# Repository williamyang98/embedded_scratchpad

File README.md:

## Embedded Scratchpad
Collection of random embedded projects

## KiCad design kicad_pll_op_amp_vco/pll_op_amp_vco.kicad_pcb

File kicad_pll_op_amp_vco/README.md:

# Introduction
Type 1 Phased Locked Loop (PLL) that synchronises to an external clock signal by divisions of 2^N for N >= 0
- 74HC4040 counter to create clock feedback signals at ```f_out = f_in/2^N```
- 74HC86 XOR to create crude digital phase detector that creates an error signal between the phase of the input and output signals
- LM358 to create variable frequency triangular wave
- LM2901 comparator to turn the triangular wave into a square signal

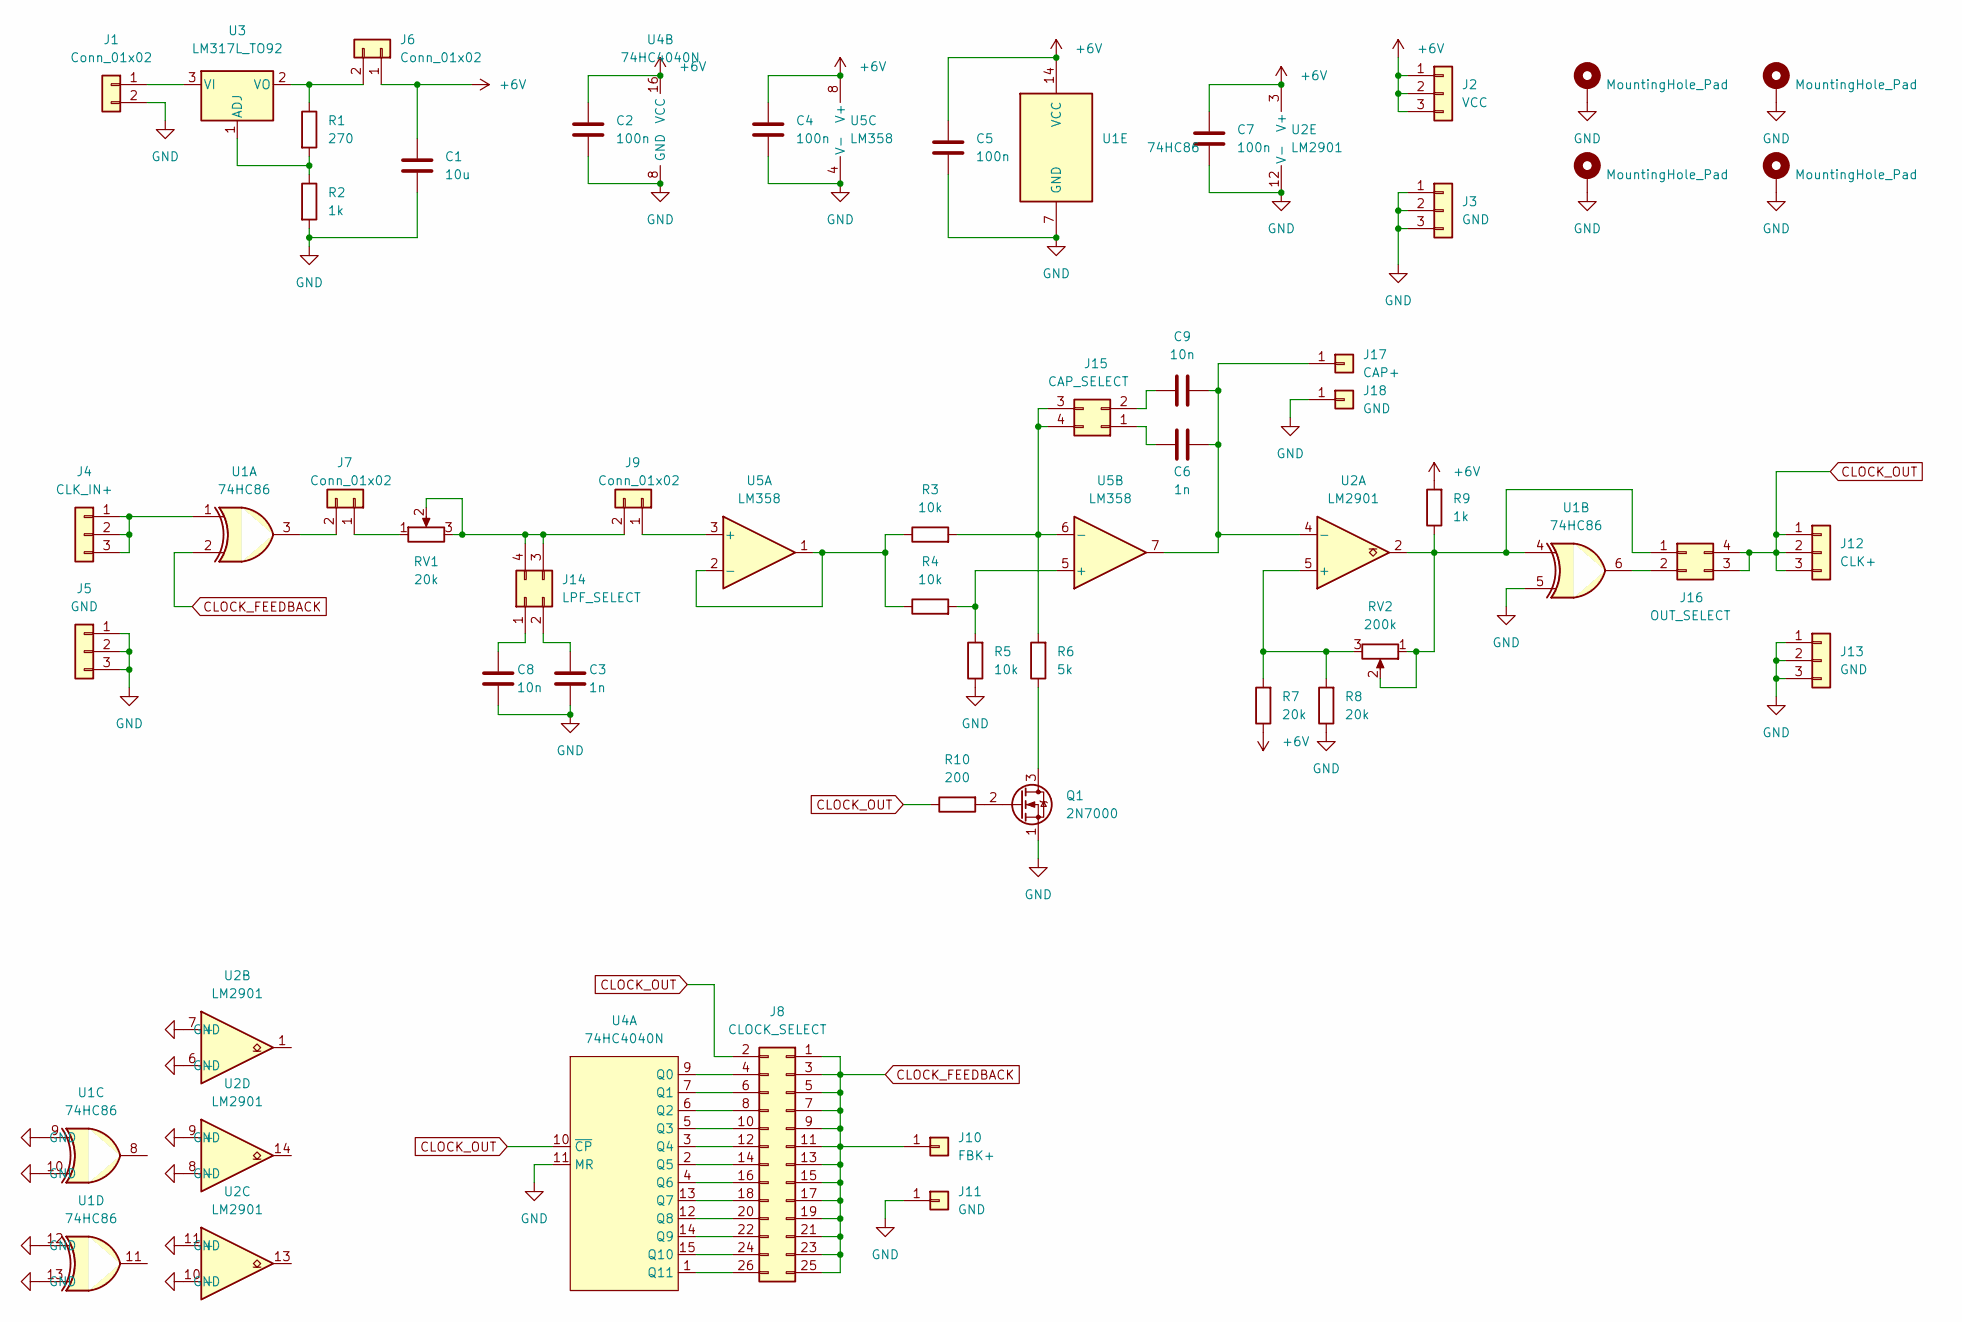
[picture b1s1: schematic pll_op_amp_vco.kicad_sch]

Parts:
C1: 10u; CP_Radial_D4.0mm_P2.00mm
C2, C4, C5, C7: 100n; C_Disc_D5.0mm_W2.5mm_P5.00mm
C3, C6: 1n; C_Disc_D5.0mm_W2.5mm_P5.00mm
C8, C9: 10n; C_Disc_D5.0mm_W2.5mm_P5.00mm
H1, H2, H3, H4: MountingHole_Pad; MountingHole_2.5mm_Pad_Via
J1: Conn_01x02; JST_EH_B2B-EH-A_1x02_P2.50mm_Vertical
J2: VCC; PinHeader_1x03_P2.54mm_Vertical
J3, J5, J13: GND; PinHeader_1x03_P2.54mm_Vertical
J4: CLK_IN+; PinHeader_1x03_P2.54mm_Vertical
J6, J7, J9: Conn_01x02; PinHeader_1x02_P2.54mm_Vertical
J8: CLOCK_SELECT; PinHeader_2x13_P2.54mm_Vertical
J10: FBK+; PinHeader_1x01_P2.54mm_Vertical
J11, J18: GND; PinHeader_1x01_P2.54mm_Vertical
J12: CLK+; PinHeader_1x03_P2.54mm_Vertical
J14: LPF_SELECT; PinHeader_2x02_P2.54mm_Vertical
J15: CAP_SELECT; PinHeader_2x02_P2.54mm_Vertical
J16: OUT_SELECT; PinHeader_2x02_P2.54mm_Vertical
J17: CAP+; PinHeader_1x01_P2.54mm_Vertical
Q1: 2N7000; TO-92_Inline
R1: 270; R_Axial_DIN0207_L6.3mm_D2.5mm_P7.62mm_Horizontal
R2, R9: 1k; R_Axial_DIN0207_L6.3mm_D2.5mm_P7.62mm_Horizontal
R3, R4, R5: 10k; R_Axial_DIN0207_L6.3mm_D2.5mm_P7.62mm_Horizontal
R6: 5k; R_Axial_DIN0207_L6.3mm_D2.5mm_P7.62mm_Horizontal
R7, R8: 20k; R_Axial_DIN0207_L6.3mm_D2.5mm_P7.62mm_Horizontal
R10: 200; R_Axial_DIN0207_L6.3mm_D2.5mm_P7.62mm_Horizontal
RV1: 20k; Potentiometer_ACP_CA9-H5_Horizontal
RV2: 200k; Potentiometer_ACP_CA9-H5_Horizontal
U1: 74HC86; DIP-14_W7.62mm_Socket_LongPads
U2: LM2901; DIP-14_W7.62mm_Socket_LongPads
U3: LM317L_TO92; TO-92_Inline
U4: 74HC4040N; DIP-16_W7.62mm_Socket_LongPads
U5: LM358; DIP-8_W7.62mm_Socket_LongPads

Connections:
+6V: C1.1, C2.2, C4.2, C5.2, C7.2, J2.1, J2.2, J2.3, J6.1, R7.1, R9.2, U1.14 (VCC), U2.3 (V+), U4.16 (VCC), U5.8 (V+)
CLOCK_FEEDBACK: J8.1, J8.3, J8.5, J8.7, J8.9, J8.11, J8.13, J8.15, J8.17, J8.19, J8.21, J8.23, J8.25, J10.1, U1.2
CLOCK_OUT: J8.2, J12.1, J12.2, J12.3, J16.3, J16.4, R10.1, U4.10 (~CP)
GND: C1.2, C2.1, C3.1, C4.1, C5.1, C7.1, C8.1, H1.1, H2.1, H3.1, H4.1, J1.2, J3.1, J3.2, J3.3, J5.1, J5.2, J5.3, J11.1, J13.1, J13.2, J13.3, J18.1, Q1.1 (S), R2.2, R5.1, R8.1, U1.5, U1.7 (GND), U1.9, U1.10, U1.12, U1.13, U2.6 (-), U2.7 (+), U2.8 (-), U2.9 (+), U2.10 (-), U2.11 (+), U2.12 (V-), U4.8 (GND), U4.11 (MR), U5.4 (V-)
unnamed: C3.2, J14.2
unnamed: C6.1, J15.1
unnamed: C6.2, C9.2, J17.1, U2.4 (-), U5.7
unnamed: C8.2, J14.1
unnamed: C9.1, J15.2
unnamed: J1.1, U3.3 (VI)
unnamed: J4.1, J4.2, J4.3, U1.1
unnamed: J6.2, R1.1, U3.2 (VO)
unnamed: J7.1, RV1.1
unnamed: J7.2, U1.3
unnamed: J8.4, U4.9 (Q0)
unnamed: J8.6, U4.7 (Q1)
unnamed: J8.8, U4.6 (Q2)
unnamed: J8.10, U4.5 (Q3)
unnamed: J8.12, U4.3 (Q4)
unnamed: J8.14, U4.2 (Q5)
unnamed: J8.16, U4.4 (Q6)
unnamed: J8.18, U4.13 (Q7)
unnamed: J8.20, U4.12 (Q8)
unnamed: J8.22, U4.14 (Q9)
unnamed: J8.24, U4.15 (Q10)
unnamed: J8.26, U4.1 (Q11)
unnamed: J9.1, U5.3 (+)
unnamed: J9.2, J14.3, J14.4, RV1.2, RV1.3
unnamed: J15.3, J15.4, R3.2, R6.2, U5.6 (-)
unnamed: J16.1, R9.1, RV2.1, RV2.2, U1.4, U2.2
unnamed: J16.2, U1.6
unnamed: Q1.2 (G), R10.2
unnamed: Q1.3 (D), R6.1
unnamed: R1.2, R2.1, U3.1 (ADJ)
unnamed: R3.1, R4.1, U5.1, U5.2 (-)
unnamed: R4.2, R5.2, U5.5 (+)
unnamed: R7.2, R8.2, RV2.3, U2.5 (+)

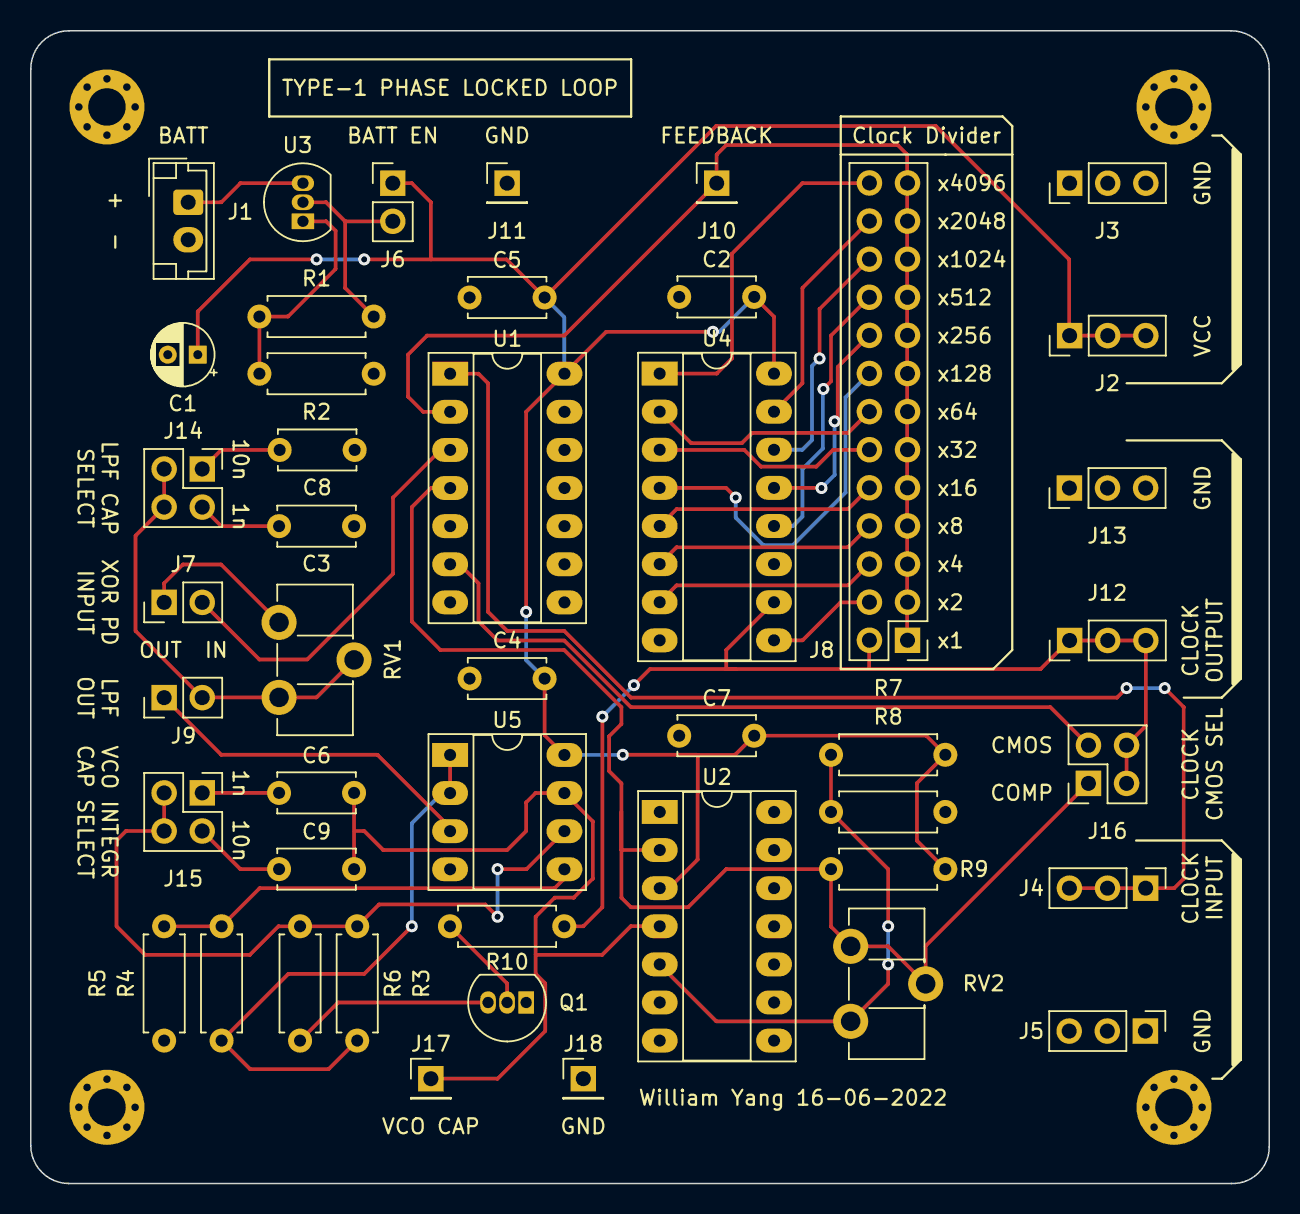
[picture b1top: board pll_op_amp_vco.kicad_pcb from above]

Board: 2 copper layers, 82.5 x 76.8 mm, 49 parts (0 on the bottom side), 37 nets.

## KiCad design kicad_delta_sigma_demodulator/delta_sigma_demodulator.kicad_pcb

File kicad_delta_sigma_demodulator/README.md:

# Introduction
Demodulates digital delta sigma serial signal into original analog signal using:
- LM319 comparators to clean up digital delta sigma 1bit signal
- LM324 op amps to create a multi-stage active low pass filter

It is the receiver board for the delta sigma modulator transmitter board in ```kicad_delta_sigma_modulator```.

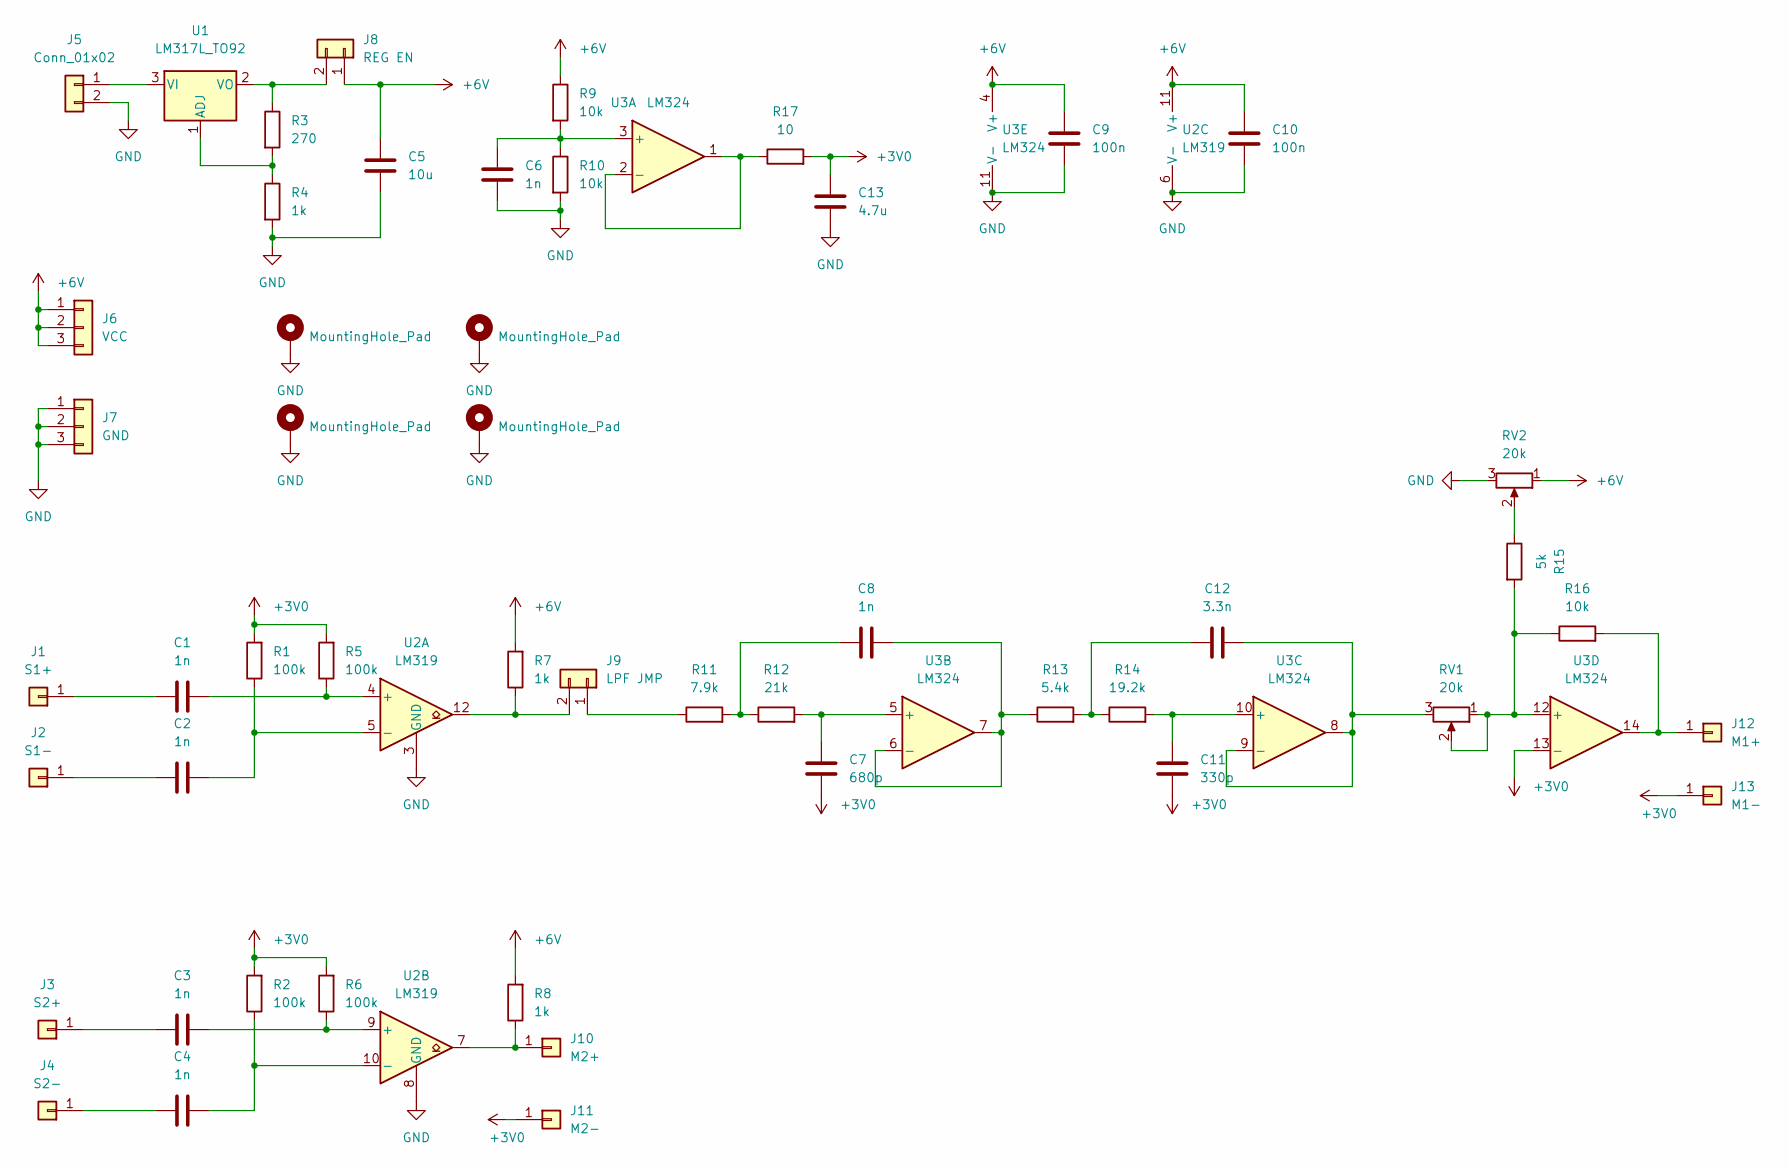
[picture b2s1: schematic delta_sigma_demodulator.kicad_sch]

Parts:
C1, C2, C3, C4, C6, C8: 1n; C_Disc_D5.0mm_W2.5mm_P5.00mm
C5: 10u; CP_Radial_D4.0mm_P2.00mm
C7: 680p; C_Disc_D5.0mm_W2.5mm_P5.00mm
C9, C10: 100n; C_Disc_D5.0mm_W2.5mm_P5.00mm
C11: 330p; C_Disc_D5.0mm_W2.5mm_P5.00mm
C12: 3.3n; C_Disc_D5.0mm_W2.5mm_P5.00mm
C13: 4.7u; CP_Radial_D4.0mm_P2.00mm
H1, H2, H3, H4: MountingHole_Pad; MountingHole_2.5mm_Pad_Via
J1: S1+; PinHeader_1x01_P2.54mm_Vertical
J2: S1-; PinHeader_1x01_P2.54mm_Vertical
J3: S2+; PinHeader_1x01_P2.54mm_Vertical
J4: S2-; PinHeader_1x01_P2.54mm_Vertical
J5: Conn_01x02; JST_EH_B2B-EH-A_1x02_P2.50mm_Vertical
J6: VCC; PinHeader_1x03_P2.54mm_Vertical
J7: GND; PinHeader_1x03_P2.54mm_Vertical
J8: REG EN; PinHeader_1x02_P2.54mm_Vertical
J9: LPF JMP; PinHeader_1x02_P2.54mm_Vertical
J10: M2+; PinHeader_1x01_P2.54mm_Vertical
J11: M2-; PinHeader_1x01_P2.54mm_Vertical
J12: M1+; PinHeader_1x01_P2.54mm_Vertical
J13: M1-; PinHeader_1x01_P2.54mm_Vertical
R1, R2, R5, R6: 100k; R_Axial_DIN0207_L6.3mm_D2.5mm_P7.62mm_Horizontal
R3: 270; R_Axial_DIN0207_L6.3mm_D2.5mm_P7.62mm_Horizontal
R4, R7, R8: 1k; R_Axial_DIN0207_L6.3mm_D2.5mm_P7.62mm_Horizontal
R9, R10, R16: 10k; R_Axial_DIN0207_L6.3mm_D2.5mm_P7.62mm_Horizontal
R11: 7.9k; R_Axial_DIN0207_L6.3mm_D2.5mm_P7.62mm_Horizontal
R12: 21k; R_Axial_DIN0207_L6.3mm_D2.5mm_P7.62mm_Horizontal
R13: 5.4k; R_Axial_DIN0207_L6.3mm_D2.5mm_P7.62mm_Horizontal
R14: 19.2k; R_Axial_DIN0207_L6.3mm_D2.5mm_P7.62mm_Horizontal
R15: 5k; R_Axial_DIN0207_L6.3mm_D2.5mm_P7.62mm_Horizontal
R17: 10; R_Axial_DIN0207_L6.3mm_D2.5mm_P7.62mm_Horizontal
RV1, RV2: 20k; Potentiometer_ACP_CA9-H5_Horizontal
U1: LM317L_TO92; TO-92_Inline
U2: LM319; DIP-14_W7.62mm_Socket_LongPads
U3: LM324; DIP-14_W7.62mm_Socket_LongPads

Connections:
+3V0: C7.2, C11.2, C13.1, J11.1, J13.1, R1.2, R2.2, R5.2, R6.2, R17.2, U3.13 (-)
+6V: C5.1, C9.2, C10.2, J6.1, J6.2, J6.3, J8.1, R7.2, R8.2, R9.1, RV2.1, U2.11 (V+), U3.4 (V+)
GND: C5.2, C6.2, C9.1, C10.1, C13.2, H1.1, H2.1, H3.1, H4.1, J5.2, J7.1, J7.2, J7.3, R4.2, R10.2, RV2.3, U2.3 (GND), U2.6 (V-), U2.8 (GND), U3.11 (V-)
unnamed: C1.1, J1.1
unnamed: C1.2, R5.1, U2.4 (+)
unnamed: C2.1, J2.1
unnamed: C2.2, R1.1, U2.5 (-)
unnamed: C3.1, J3.1
unnamed: C3.2, R6.1, U2.9 (+)
unnamed: C4.1, J4.1
unnamed: C4.2, R2.1, U2.10 (-)
unnamed: C6.1, R9.2, R10.1, U3.3 (+)
unnamed: C7.1, R12.2, U3.5 (+)
unnamed: C8.1, R11.2, R12.1
unnamed: C8.2, R13.1, U3.6 (-), U3.7
unnamed: C11.1, R14.2, U3.10 (+)
unnamed: C12.1, R13.2, R14.1
unnamed: C12.2, RV1.3, U3.8, U3.9 (-)
unnamed: J5.1, U1.3 (VI)
unnamed: J8.2, R3.1, U1.2 (VO)
unnamed: J9.1, R11.1
unnamed: J9.2, R7.1, U2.12
unnamed: R3.2, R4.1, U1.1 (ADJ)
unnamed: J10.1, R8.1, U2.7
unnamed: R15.1, RV2.2
unnamed: R15.2, R16.1, RV1.1, RV1.2, U3.12 (+)
unnamed: J12.1, R16.2, U3.14
unnamed: R17.1, U3.1, U3.2 (-)

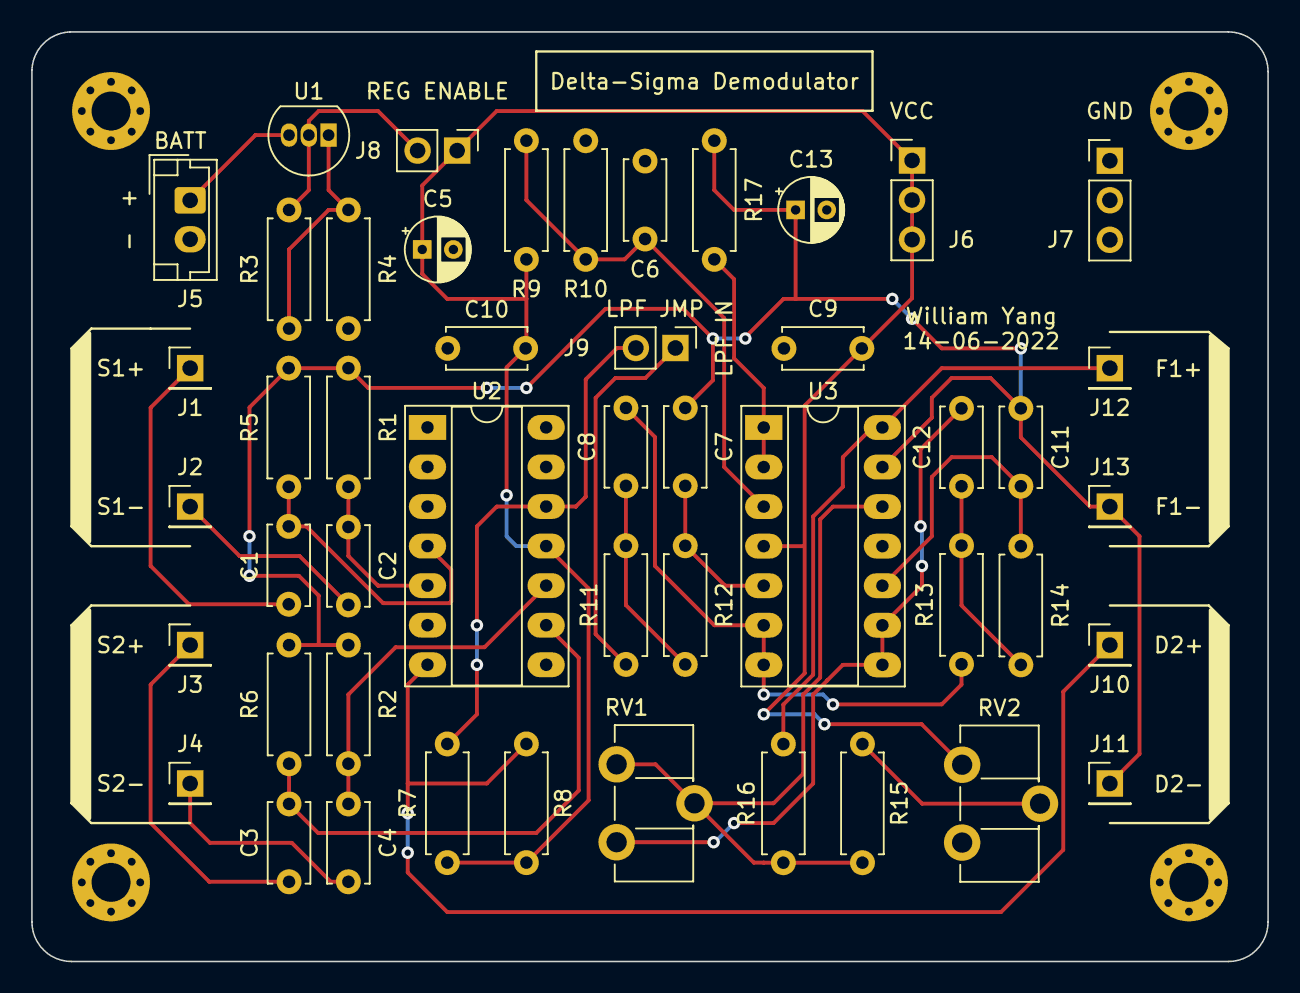
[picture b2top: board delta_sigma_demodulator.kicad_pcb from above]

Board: 2 copper layers, 79.4 x 59.7 mm, 52 parts (0 on the bottom side), 28 nets.

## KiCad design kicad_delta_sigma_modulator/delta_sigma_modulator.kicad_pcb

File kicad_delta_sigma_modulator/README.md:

# Introduction
Modulates analog signal into serial delta sigma 1bit digital signal:
- LM556 to generate the clock signal for the 1bit delta sigma ADC
- 74HC74 D Flip-Flop to act as a 1bit ADC
- LM324 op amps to amplify and bias the signal to the correct voltage for the delta sigma modulator
- TL072 moderate bandwidth op amp for the delta sigma modulator's integrator
- LM319 comparator to turn triangular integral signal from TL072 into digital signal that will be latched by the 74HC74
- LM324 to generate a virtual ground to split the single positive supply rail in half
- LM317 to provided regulated voltage to the board from a 9V battery

It is the transmitter board for the delta sigma demodulator receiver board in ```kicad_delta_sigma_demodulator```.

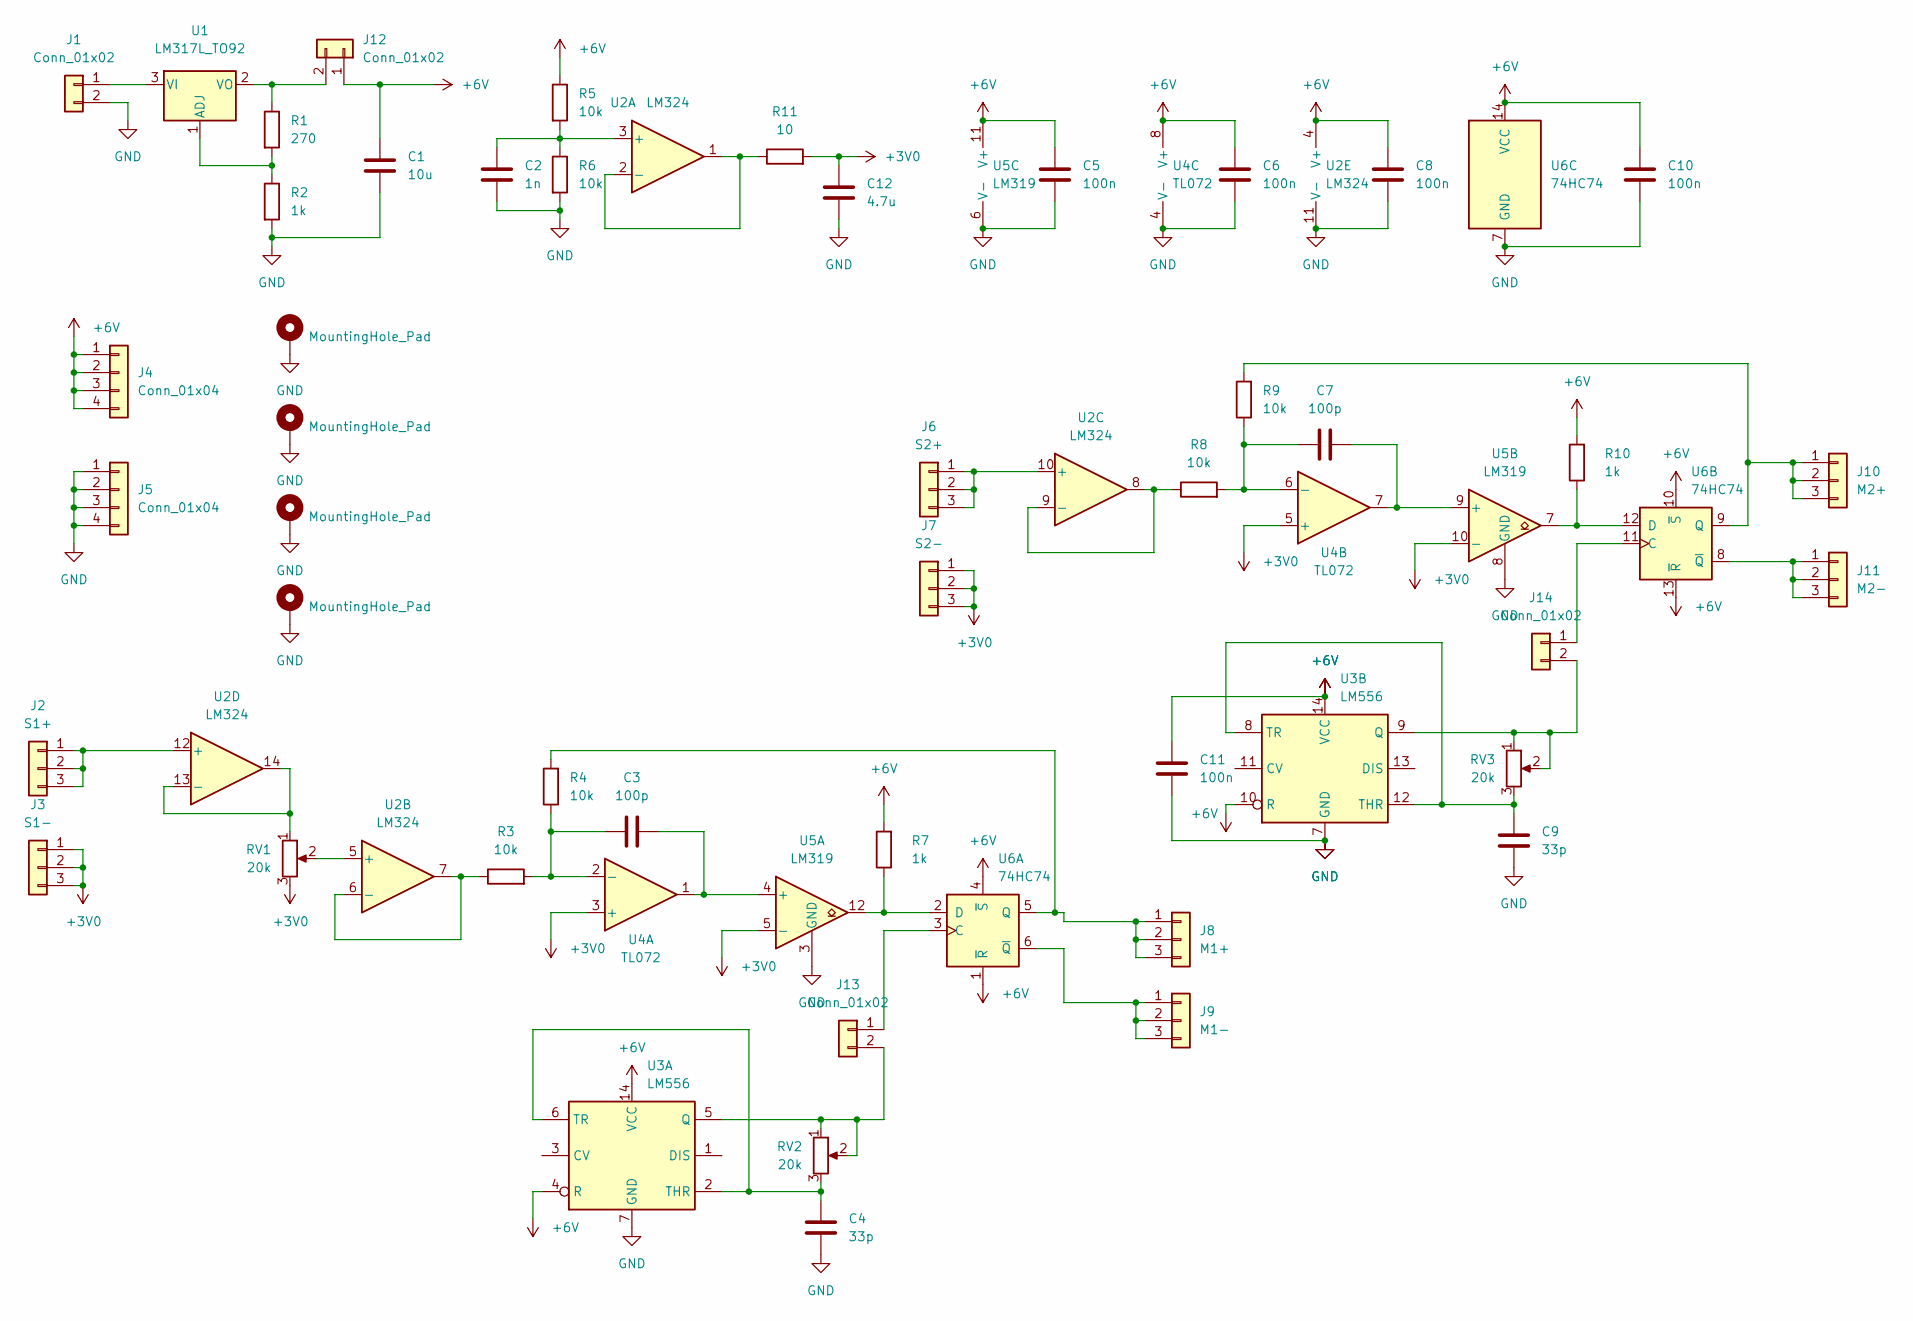
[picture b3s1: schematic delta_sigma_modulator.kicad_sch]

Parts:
C1: 10u; CP_Radial_D4.0mm_P2.00mm
C2: 1n; C_Disc_D5.0mm_W2.5mm_P5.00mm
C3, C7: 100p; C_Disc_D5.0mm_W2.5mm_P5.00mm
C4, C9: 33p; C_Disc_D5.0mm_W2.5mm_P5.00mm
C5, C6, C8, C10, C11: 100n; C_Disc_D5.0mm_W2.5mm_P5.00mm
C12: 4.7u; CP_Radial_D4.0mm_P2.00mm
H1, H2, H3, H4: MountingHole_Pad; MountingHole_2.5mm_Pad_Via
J1: Conn_01x02; JST_EH_B2B-EH-A_1x02_P2.50mm_Vertical
J2: S1+; PinHeader_1x03_P2.54mm_Vertical
J3: S1-; PinHeader_1x03_P2.54mm_Vertical
J4, J5: Conn_01x04; PinHeader_1x04_P2.54mm_Vertical
J6: S2+; PinHeader_1x03_P2.54mm_Vertical
J7: S2-; PinHeader_1x03_P2.54mm_Vertical
J8: M1+; PinHeader_1x03_P2.54mm_Vertical
J9: M1-; PinHeader_1x03_P2.54mm_Vertical
J10: M2+; PinHeader_1x03_P2.54mm_Vertical
J11: M2-; PinHeader_1x03_P2.54mm_Vertical
J12, J13, J14: Conn_01x02; PinHeader_1x02_P2.54mm_Vertical
R1: 270; R_Axial_DIN0207_L6.3mm_D2.5mm_P7.62mm_Horizontal
R2, R7, R10: 1k; R_Axial_DIN0207_L6.3mm_D2.5mm_P7.62mm_Horizontal
R3, R4, R5, R6, R8, R9: 10k; R_Axial_DIN0207_L6.3mm_D2.5mm_P7.62mm_Horizontal
R11: 10; R_Axial_DIN0207_L6.3mm_D2.5mm_P7.62mm_Horizontal
RV1, RV2, RV3: 20k; Potentiometer_ACP_CA9-H5_Horizontal
U1: LM317L_TO92; TO-92_Inline
U2: LM324; DIP-14_W7.62mm_Socket_LongPads
U3: LM556; DIP-14_W7.62mm_Socket_LongPads
U4: TL072; DIP-8_W7.62mm_Socket_LongPads
U5: LM319; DIP-14_W7.62mm_Socket_LongPads
U6: 74HC74; DIP-14_W7.62mm_Socket_LongPads

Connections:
+3V0: C12.1, J3.1, J3.2, J3.3, J7.1, J7.2, J7.3, R11.2, RV1.3, U4.3 (+), U4.5 (+), U5.5 (-), U5.10 (-)
+6V: C1.1, C5.2, C6.2, C8.2, C10.2, C11.2, J4.1, J4.2, J4.3, J4.4, J12.1, R5.1, R7.2, R10.2, U2.4 (V+), U3.4 (R), U3.10 (R), U3.14 (VCC), U4.8 (V+), U5.11 (V+), U6.1 (~R), U6.4 (~S), U6.10 (~S), U6.13 (~R), U6.14 (VCC)
GND: C1.2, C2.2, C4.1, C5.1, C6.1, C8.1, C9.1, C10.1, C11.1, C12.2, H1.1, H2.1, H3.1, H4.1, J1.2, J5.1, J5.2, J5.3, J5.4, R2.2, R6.2, U2.11 (V-), U3.7 (GND), U4.4 (V-), U5.3 (GND), U5.6 (V-), U5.8 (GND), U6.7 (GND)
unnamed: C2.1, R5.2, R6.1, U2.3 (+)
unnamed: C3.1, R3.2, R4.1, U4.2 (-)
unnamed: C3.2, U4.1, U5.4 (+)
unnamed: C4.2, RV2.3, U3.2 (THR), U3.6 (TR)
unnamed: C7.1, R8.2, R9.1, U4.6 (-)
unnamed: C7.2, U4.7, U5.9 (+)
unnamed: C9.2, RV3.3, U3.8 (TR), U3.12 (THR)
unnamed: J1.1, U1.3 (VI)
unnamed: J2.1, J2.2, J2.3, U2.12 (+)
unnamed: J6.1, J6.2, J6.3, U2.10 (+)
unnamed: J8.1, J8.2, J8.3, R4.2, U6.5 (Q)
unnamed: J9.1, J9.2, J9.3, U6.6 (~Q)
unnamed: J10.1, J10.2, J10.3, R9.2, U6.9 (Q)
unnamed: J11.1, J11.2, J11.3, U6.8 (~Q)
unnamed: J12.2, R1.1, U1.2 (VO)
unnamed: J13.1, U6.3 (C)
unnamed: J13.2, RV2.1, RV2.2, U3.5 (Q)
unnamed: J14.1, U6.11 (C)
unnamed: J14.2, RV3.1, RV3.2, U3.9 (Q)
unnamed: R1.2, R2.1, U1.1 (ADJ)
unnamed: R3.1, U2.6 (-), U2.7
unnamed: R7.1, U5.12, U6.2 (D)
unnamed: R8.1, U2.8, U2.9 (-)
unnamed: R10.1, U5.7, U6.12 (D)
unnamed: R11.1, U2.1, U2.2 (-)
unnamed: RV1.1, U2.13 (-), U2.14
unnamed: RV1.2, U2.5 (+)

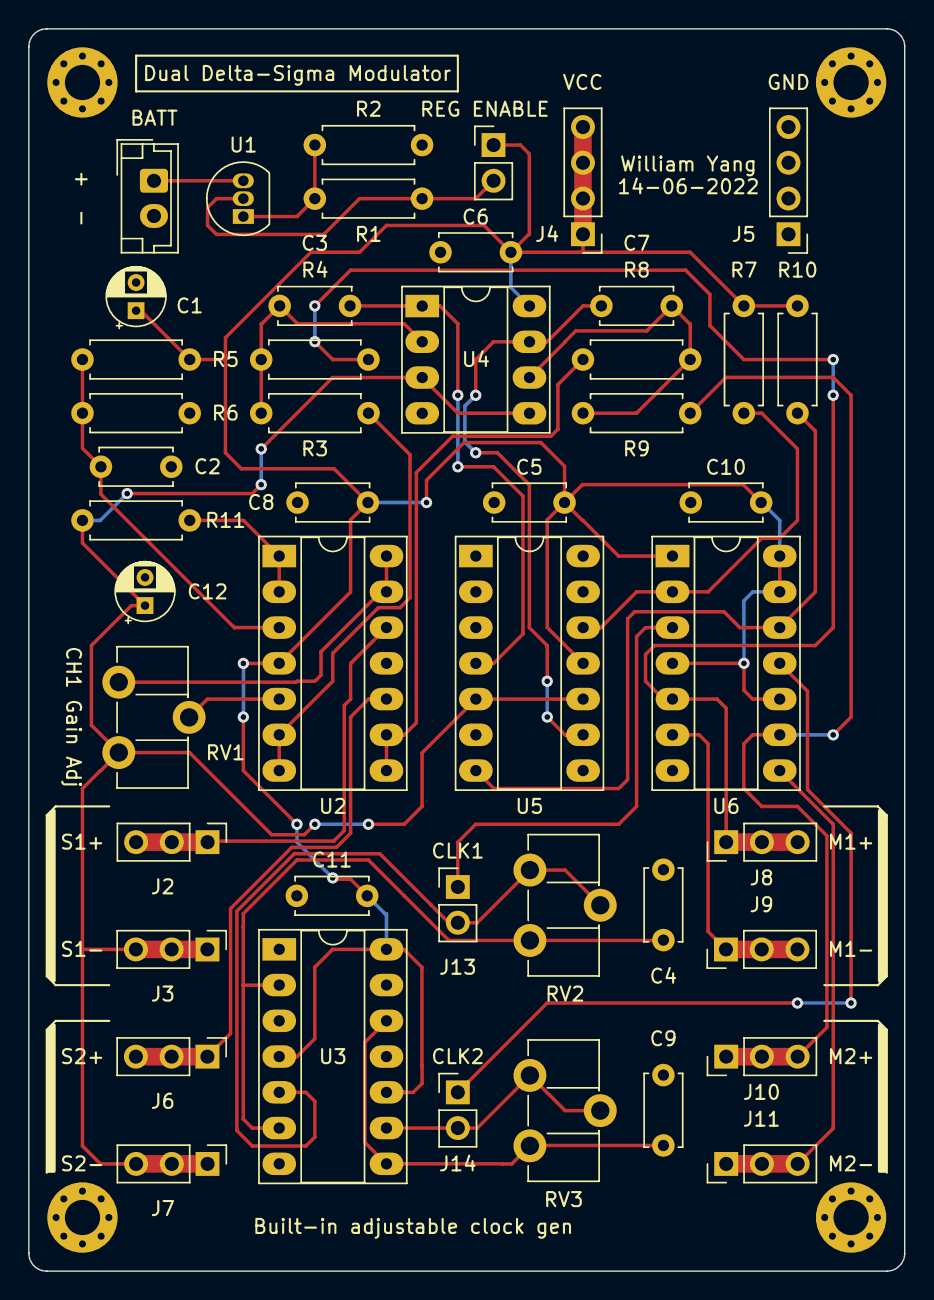
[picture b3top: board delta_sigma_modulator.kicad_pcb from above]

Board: 2 copper layers, 62.2 x 88.3 mm, 50 parts (0 on the bottom side), 30 nets.

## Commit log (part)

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2025-10-24 Added initial project
2025-10-24 Added shift lcd arduino uno sketch
2026-06-26 Added st7789 basic demo
2026-06-26 Write to spi without arduino core slowing things down
2026-06-26 Replace spi poll with nops assuming fixed frequency
2026-06-26 Removed adafruit library
2026-06-27 Add adafruit demo
2026-06-29 Added st7789 test harness
2026-06-29 Added README.md
2026-06-30 Refactored arduino code
2026-06-30 Added circle demo
